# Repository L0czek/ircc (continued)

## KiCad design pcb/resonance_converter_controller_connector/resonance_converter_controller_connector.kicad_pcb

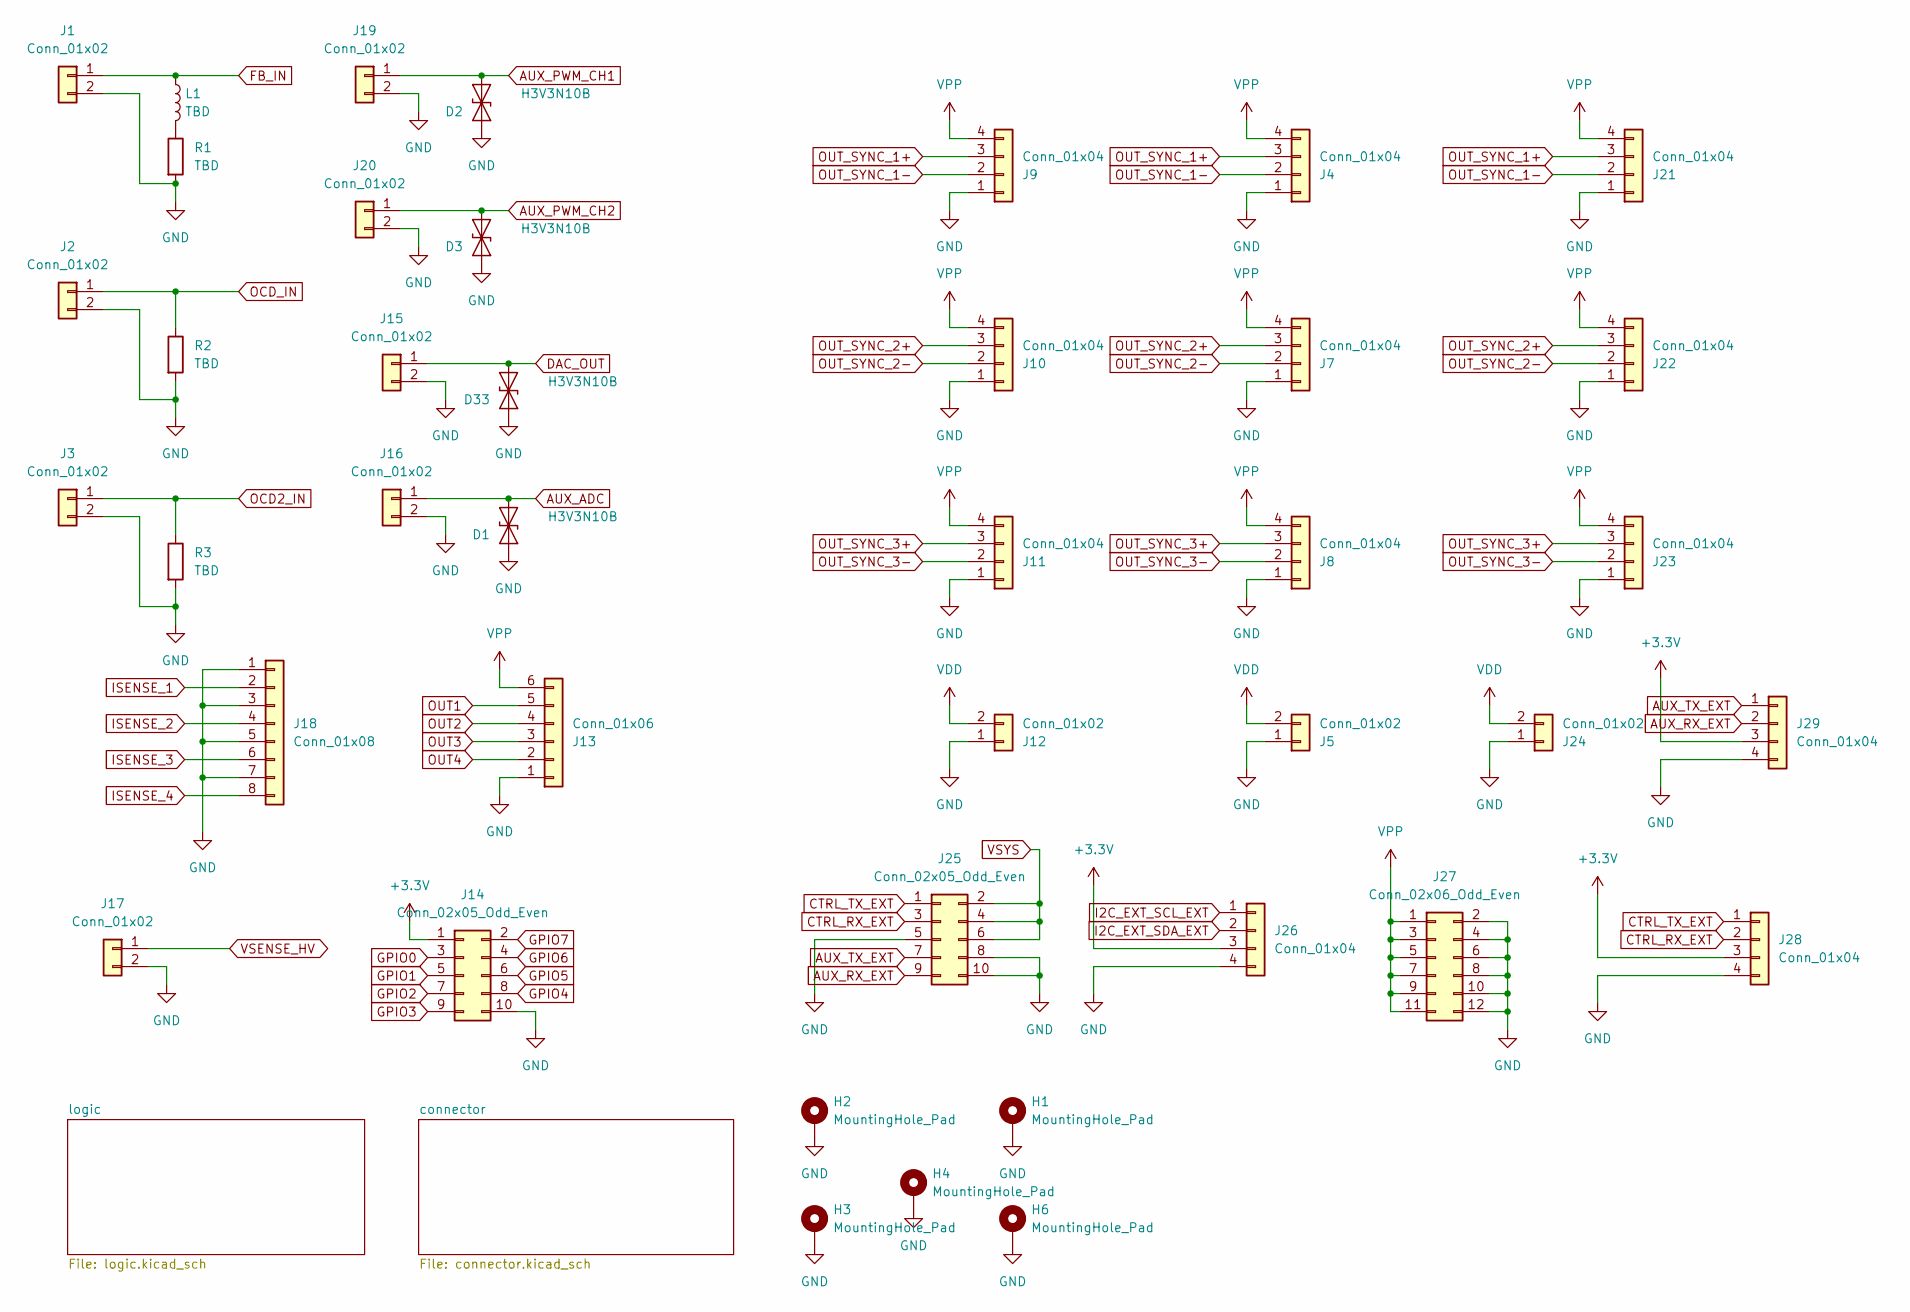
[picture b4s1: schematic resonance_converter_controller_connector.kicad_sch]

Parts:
D1, D2, D3, D33: H3V3N10B; D_0402_1005Metric; LCSC Part C20617909
H1, H2, H3, H4, H6: MountingHole_Pad; MountingHole_2.2mm_M2_Pad_Via
J1, J2, J3, J15, J16, J17, J19, J20: Conn_01x02; PhoenixContact_MCV_1,5_2-G-5.08_1x02_P5.08mm_Vertical
J4, J7, J8, J9, J10, J11, J21, J22, J23, J26, J28, J29: Conn_01x04; JST_PH_B4B-PH-K_1x04_P2.00mm_Vertical
J5, J12, J24: Conn_01x02; AMASS_XT30U-M_1x02_P5.0mm_Vertical
J13: Conn_01x06; JST_PH_B6B-PH-K_1x06_P2.00mm_Vertical
J14, J25: Conn_02x05_Odd_Even; PinHeader_2x05_P2.54mm_Vertical
J18: Conn_01x08; PhoenixContact_MCV_1,5_8-G-3.5_1x08_P3.50mm_Vertical
J27: Conn_02x06_Odd_Even; PinHeader_2x06_P2.54mm_Vertical
L1: TBD; L_Radial_D12.0mm_P10.00mm_Neosid_SD12_style1
R1, R2, R3: TBD; TO-220-2_Vertical

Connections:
+3.3V: J14.1, J26.3, J28.3, J29.3; also elsewhere on the board
AUX_ADC: D1.1 (A1), J16.1; also elsewhere on the board
AUX_PWM_CH1: D2.1 (A1), J19.1; also elsewhere on the board
AUX_PWM_CH2: D3.1 (A1), J20.1; also elsewhere on the board
AUX_RX_EXT: J25.9, J29.2; also elsewhere on the board
AUX_TX_EXT: J25.7, J29.1; also elsewhere on the board
CTRL_RX_EXT: J25.3, J28.2; also elsewhere on the board
CTRL_TX_EXT: J25.1, J28.1; also elsewhere on the board
DAC_OUT: D33.1 (A1), J15.1; also elsewhere on the board
FB_IN: J1.1, L1.1; also elsewhere on the board
GND: D1.2 (A2), D2.2 (A2), D3.2 (A2), D33.2 (A2), H1.1 (1_1), H2.1 (1_1), H3.1 (1_1), H4.1 (1_1), H6.1 (1_1), J1.2, J2.2, J3.2, J4.1, J5.1, J7.1, J8.1, J9.1, J10.1, J11.1, J12.1, J13.1, J14.10, J15.2, J16.2, J17.2, J18.1, J18.3, J18.5, J18.7, J19.2, J20.2, J21.1, J22.1, J23.1, J24.1, J25.5, J25.8, J25.10, J26.4, J27.2, J27.4, J27.6, J27.8, J27.10, J27.12, J28.4, J29.4, R1.2, R2.2, R3.2; also elsewhere on the board
GPIO0: J14.3; also elsewhere on the board
GPIO1: J14.5; also elsewhere on the board
GPIO2: J14.7; also elsewhere on the board
GPIO3: J14.9; also elsewhere on the board
GPIO4: J14.8; also elsewhere on the board
GPIO5: J14.6; also elsewhere on the board
GPIO6: J14.4; also elsewhere on the board
GPIO7: J14.2; also elsewhere on the board
I2C_EXT_SCL_EXT: J26.1; also elsewhere on the board
I2C_EXT_SDA_EXT: J26.2; also elsewhere on the board
ISENSE_1: J18.2; also elsewhere on the board
ISENSE_2: J18.4; also elsewhere on the board
ISENSE_3: J18.6; also elsewhere on the board
ISENSE_4: J18.8; also elsewhere on the board
unnamed: L1.2, R1.1
OCD2_IN: J3.1, R3.1; also elsewhere on the board
OCD_IN: J2.1, R2.1; also elsewhere on the board
OUT1: J13.5; also elsewhere on the board
OUT2: J13.4; also elsewhere on the board
OUT3: J13.3; also elsewhere on the board
OUT4: J13.2; also elsewhere on the board
OUT_SYNC_1+: J4.3, J9.3, J21.3; also elsewhere on the board
OUT_SYNC_1-: J4.2, J9.2, J21.2; also elsewhere on the board
OUT_SYNC_2+: J7.3, J10.3, J22.3; also elsewhere on the board
OUT_SYNC_2-: J7.2, J10.2, J22.2; also elsewhere on the board
OUT_SYNC_3+: J8.3, J11.3, J23.3; also elsewhere on the board
OUT_SYNC_3-: J8.2, J11.2, J23.2; also elsewhere on the board
VDD: J5.2, J12.2, J24.2; also elsewhere on the board
VPP: J4.4, J7.4, J8.4, J9.4, J10.4, J11.4, J13.6, J21.4, J22.4, J23.4, J27.1, J27.3, J27.5, J27.7, J27.9, J27.11; also elsewhere on the board
VSENSE_HV: J17.1; also elsewhere on the board
VSYS: J25.2, J25.4, J25.6; also elsewhere on the board

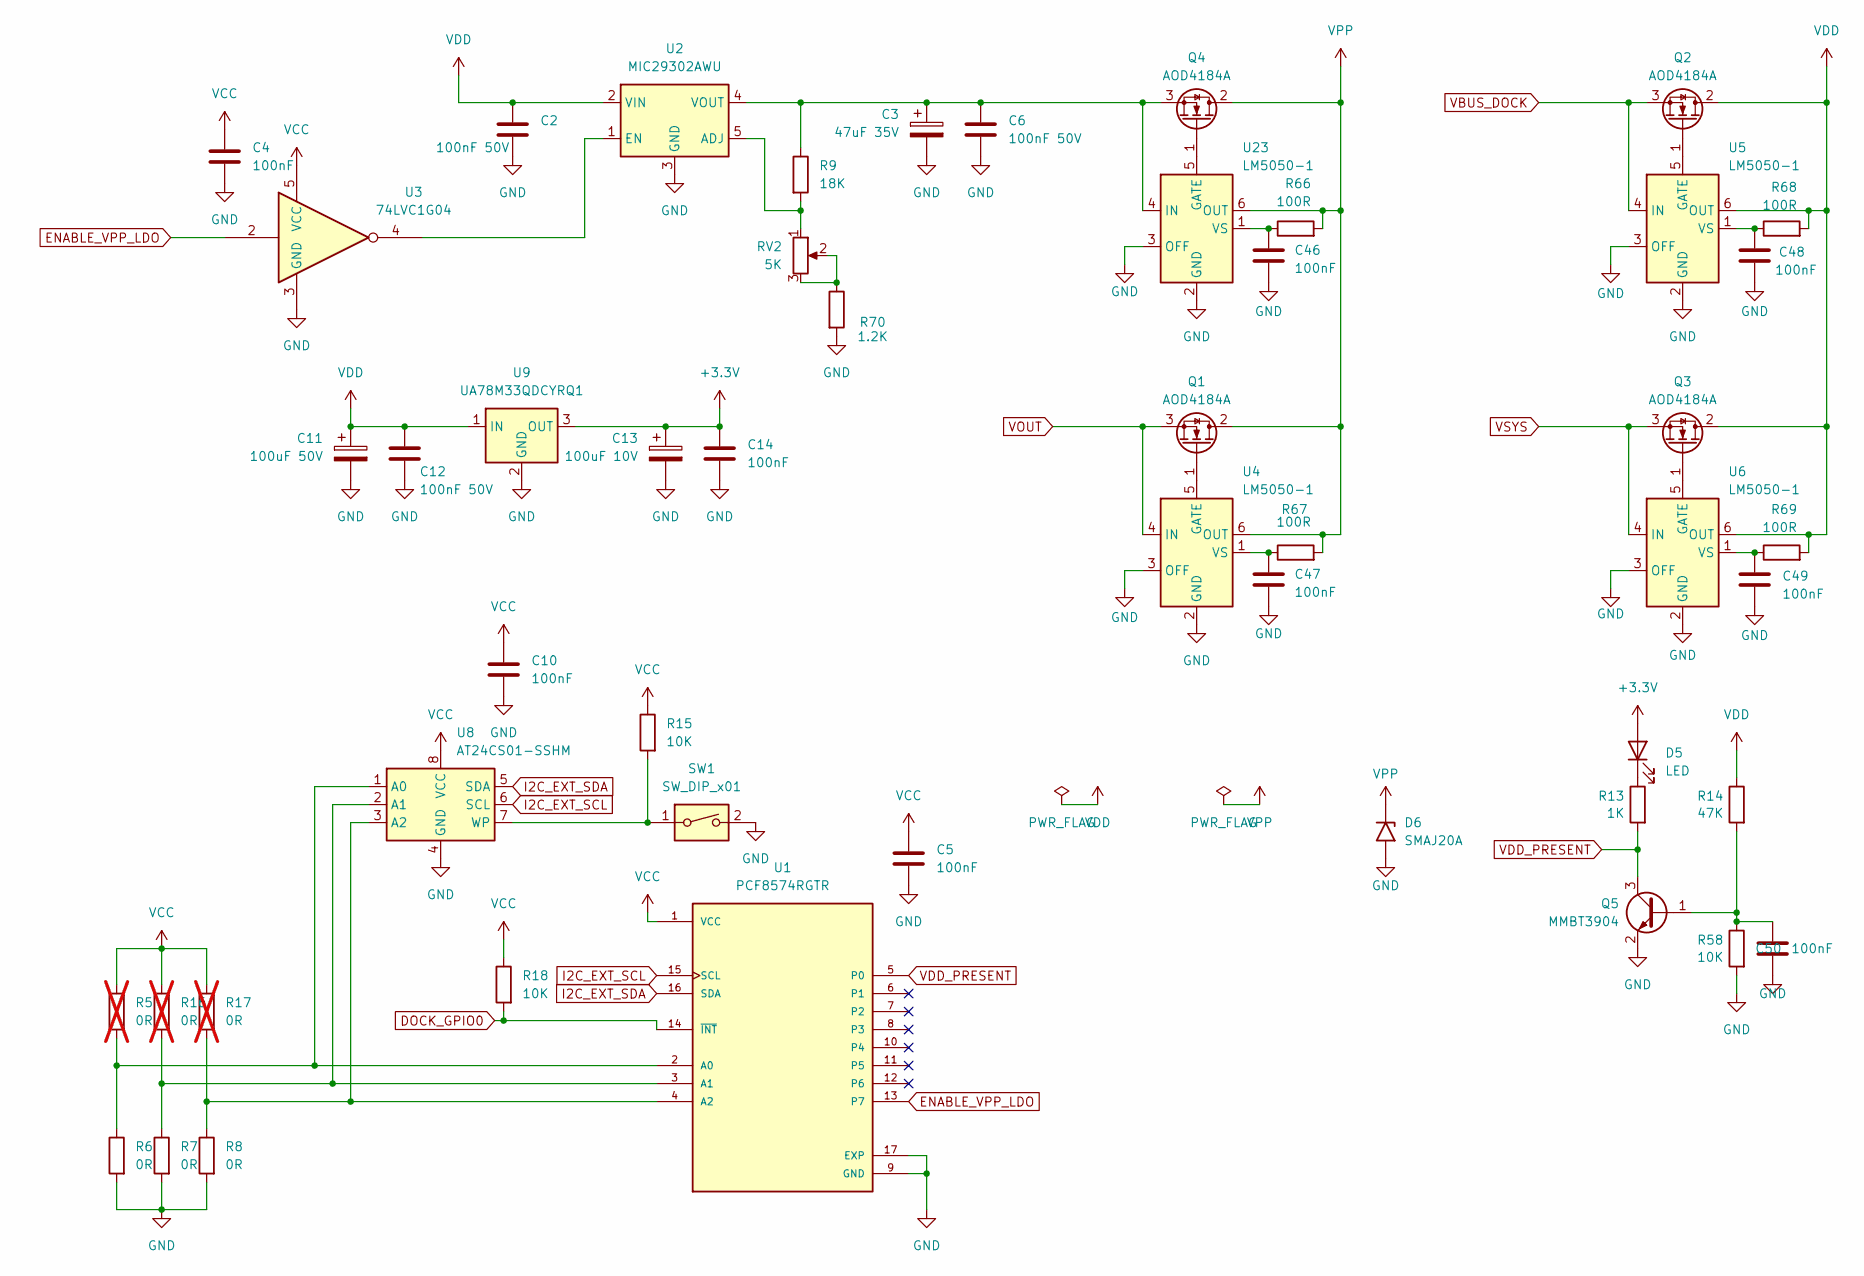
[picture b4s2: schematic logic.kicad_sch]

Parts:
C2, C6, C12: 100nF 50V; C_0603_1608Metric; LCSC Part C14663
C3: 47uF 35V; CP_Elec_10x10
C4, C5, C10, C14, C50: 100nF; C_0402_1005Metric; LCSC Part C307331
C11: 100uF 50V; CP_Elec_10x10
C13: 100uF 10V; CP_Elec_10x10
C46, C47, C48, C49: 100nF; C_0603_1608Metric; LCSC Part C14663
D5: LED; LED_1206_3216Metric
D6: SMAJ20A; D_SMA; MPN SMAJ20A; LCSC Part C41376408
Q1, Q2, Q3, Q4: AOD4184A; TO-252-2; MPN AOD4184A; LCSC Part C22367195
Q5: MMBT3904; SOT-23; MPN MMBT3904; LCSC Part C20526
R5, R16, R17: 0R; R_0402_1005Metric; LCSC Part C17168; not fitted
R6, R7, R8: 0R; R_0402_1005Metric; LCSC Part C17168
R9: 18K; R_0402_1005Metric; LCSC Part C25762
R13: 1K; R_0402_1005Metric; LCSC Part C11702
R14: 47K; R_0402_1005Metric; LCSC Part C25792
R15, R18, R58: 10K; R_0402_1005Metric; LCSC Part C25744
R66, R67, R68, R69: 100R; R_0402_1005Metric; LCSC Part C25076
R70: 1.2K; R_0402_1005Metric; LCSC Part C25862
RV2: 5K; Potentiometer_Bourns_3269W_Vertical
SW1: SW_DIP_x01; SW_DIP_SPSTx01_Slide_9.78x4.72mm_W8.61mm_P2.54mm
U1: PCF8574RGTR; QFN50P300X300X100-17N; PARTREV J; DigiKey_Part_Number 296-21238-1-ND
U2: MIC29302AWU; TO-263-5_TabPin3
U3: 74LVC1G04; SOT-23-5
U4, U5, U6, U23: LM5050-1; TSOT-23-6; MPN LM5050MK-1/NOPB; LCSC Part C129323
U8: AT24CS01-SSHM; SOIC-8_3.9x4.9mm_P1.27mm
U9: UA78M33QDCYRQ1; SOT-223-3_TabPin2

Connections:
+3.3V: C13.1, C14.1, D5.2 (A), U9.3 (OUT); also elsewhere on the board
DOCK_GPIO0: R18.2, U1.14 (~INT)
ENABLE_VPP_LDO: U1.13 (P7), U3.2
GND: C2.2, C3.2, C4.2, C5.2, C6.2, C10.2, C11.2, C12.2, C13.2, C14.2, C46.2, C47.2, C48.2, C49.2, C50.2, D6.2 (A2), Q5.2 (E), R6.2, R7.2, R8.2, R58.2, R70.2, SW1.2, U1.9 (GND), U1.17 (EXP), U2.3 (GND), U3.3 (GND), U4.2 (GND), U4.3 (OFF), U5.2 (GND), U5.3 (OFF), U6.2 (GND), U6.3 (OFF), U8.4 (GND), U9.2 (GND), U23.2 (GND), U23.3 (OFF); also elsewhere on the board
I2C_EXT_SCL: U1.15 (SCL), U8.6 (SCL); also elsewhere on the board
I2C_EXT_SDA: U1.16 (SDA), U8.5 (SDA); also elsewhere on the board
unnamed: D5.1 (K), R13.1
unnamed: Q1.1 (G), U4.5 (GATE)
unnamed: Q2.1 (G), U5.5 (GATE)
unnamed: Q3.1 (G), U6.5 (GATE)
unnamed: Q4.1 (G), U23.5 (GATE)
unnamed: C3.1, C6.1, Q4.3 (S), R9.1, U2.4 (VOUT), U23.4 (IN)
unnamed: C50.1, Q5.1 (B), R14.2, R58.1
unnamed: R70.1, RV2.2, RV2.3
unnamed: R5.2, R6.1, U1.2 (A0), U8.1 (A0)
unnamed: R7.1, R16.2, U1.3 (A1), U8.2 (A1)
unnamed: R8.1, R17.2, U1.4 (A2), U8.3 (A2)
unnamed: R9.2, RV2.1, U2.5 (ADJ)
unnamed: U2.1 (EN), U3.4
unnamed: C47.1, R67.1, U4.1 (VS)
unnamed: C48.1, R68.1, U5.1 (VS)
unnamed: C49.1, R69.1, U6.1 (VS)
unnamed: R15.2, SW1.1, U8.7 (WP)
unnamed: C46.1, R66.1, U23.1 (VS)
VBUS_DOCK: Q2.3 (S), U5.4 (IN); also elsewhere on the board
VCC: C4.1, C5.1, C10.1, R5.1, R15.1, R16.1, R17.1, R18.1, U1.1 (VCC), U3.5 (VCC), U8.8 (VCC); also elsewhere on the board
VDD: C2.1, C11.1, C12.1, Q2.2 (D), Q3.2 (D), R14.1, R68.2, R69.2, U2.2 (VIN), U5.6 (OUT), U6.6 (OUT), U9.1 (IN); also elsewhere on the board
VDD_PRESENT: Q5.3 (C), R13.2, U1.5 (P0)
VOUT: Q1.3 (S), U4.4 (IN); also elsewhere on the board
VPP: D6.1 (A1), Q1.2 (D), Q4.2 (D), R66.2, R67.2, U4.6 (OUT), U23.6 (OUT); also elsewhere on the board
VSYS: Q3.3 (S), U6.4 (IN); also elsewhere on the board

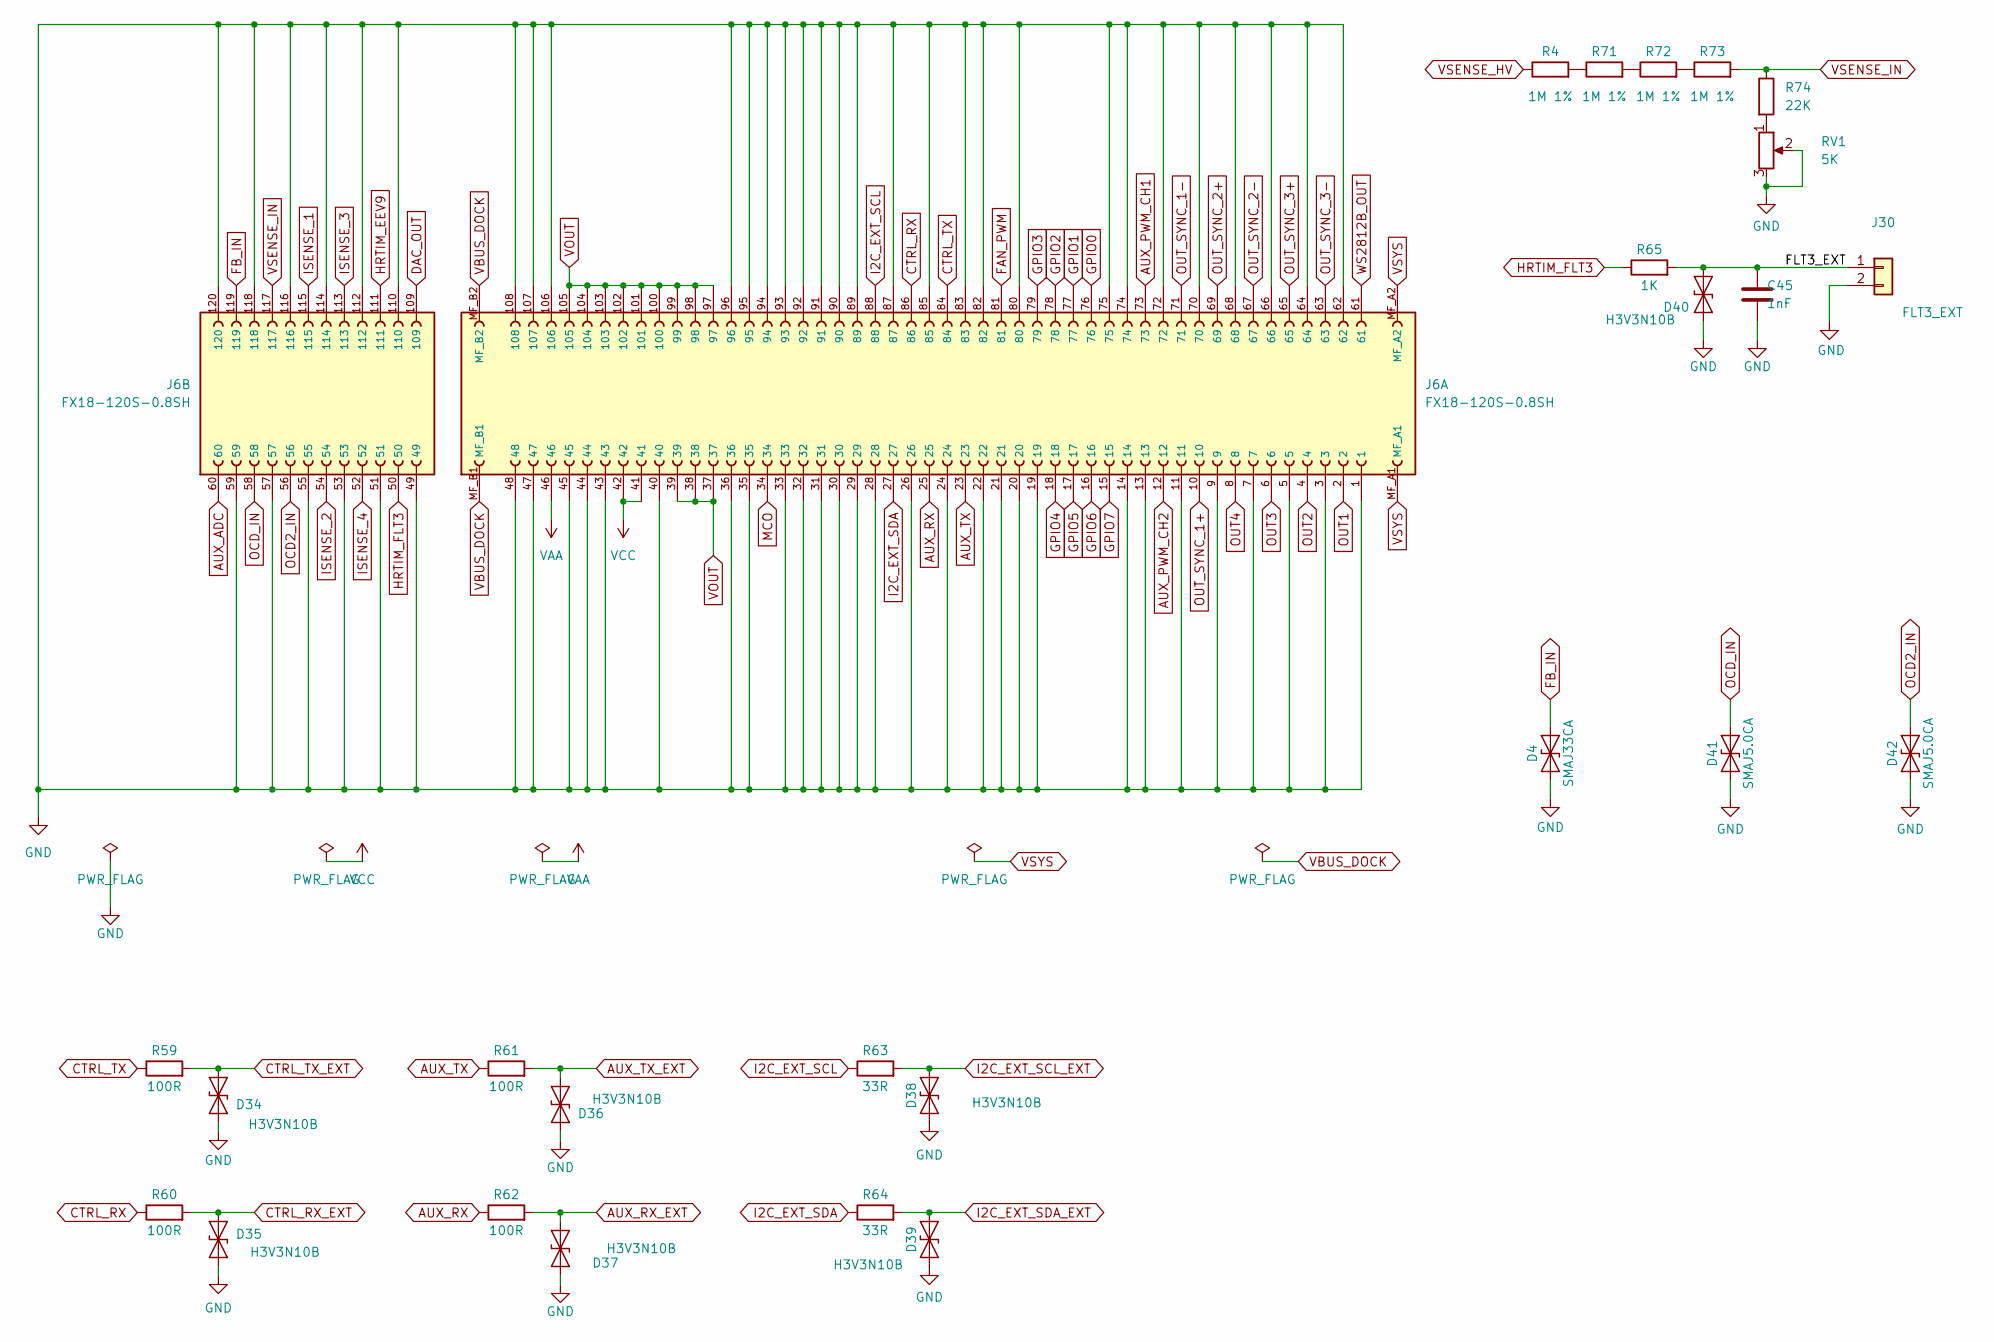
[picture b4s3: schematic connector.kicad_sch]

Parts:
C45: 1nF; C_0402_1005Metric; LCSC Part C1523
D4: SMAJ33CA; D_SMA; MPN SMAJ33CA; LCSC Part C19077549
D34, D35, D36, D37, D38, D39, D40: H3V3N10B; D_0402_1005Metric; LCSC Part C20617909
D41, D42: SMAJ5.0CA; D_SMA; MPN SMAJ5.0CA; LCSC Part C19077524
J6: FX18-120S-0.8SH; HIROSE_FX18-120S-0.8SH; PARTREV 1
J30: FLT3_EXT; PinHeader_1x02_P2.54mm_Vertical
R4, R71, R72, R73: 1M 1%; R_1206_3216Metric; LCSC Part C17927
R59, R60, R61, R62: 100R; R_0402_1005Metric; LCSC Part C25076
R63, R64: 33R; R_0402_1005Metric; LCSC Part C25105
R65: 1K; R_0402_1005Metric; LCSC Part C11702
R74: 22K; R_0402_1005Metric; LCSC Part C25768
RV1: 5K; Potentiometer_Bourns_3269W_Vertical

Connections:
/connector/FLT3_EXT: C45.1, D40.2 (A2), J30.1, R65.2
AUX_ADC: J6.60; also elsewhere on the board
AUX_PWM_CH1: J6.73; also elsewhere on the board
AUX_PWM_CH2: J6.12; also elsewhere on the board
AUX_RX: J6.25, R62.1
AUX_RX_EXT: D37.2 (A2), R62.2; also elsewhere on the board
AUX_TX: J6.23, R61.1
AUX_TX_EXT: D36.2 (A2), R61.2; also elsewhere on the board
CTRL_RX: J6.86, R60.1
CTRL_RX_EXT: D35.2 (A2), R60.2; also elsewhere on the board
CTRL_TX: J6.84, R59.1
CTRL_TX_EXT: D34.2 (A2), R59.2; also elsewhere on the board
DAC_OUT: J6.109; also elsewhere on the board
FAN_PWM: J6.81
FB_IN: D4.2 (A2), J6.119; also elsewhere on the board
GND: C45.2, D4.1 (A1), D34.1 (A1), D35.1 (A1), D36.1 (A1), D37.1 (A1), D38.1 (A1), D39.1 (A1), D40.1 (A1), D41.1 (A1), D42.1 (A1), J6.1, J6.3, J6.5, J6.7, J6.9, J6.11, J6.13, J6.14, J6.19, J6.20, J6.21, J6.22, J6.24, J6.26, J6.28, J6.29, J6.30, J6.31, J6.32, J6.33, J6.35, J6.36, J6.40, J6.43, J6.44, J6.45, J6.47, J6.48, J6.49, J6.51, J6.53, J6.55, J6.57, J6.59, J6.62, J6.64, J6.66, J6.68, J6.70, J6.72, J6.74, J6.75, J6.80, J6.82, J6.83, J6.85, J6.87, J6.89, J6.90, J6.91, J6.92, J6.93, J6.94, J6.95, J6.96, J6.106, J6.107, J6.108, J6.110, J6.112, J6.114, J6.116, J6.118, J6.120, J30.2, RV1.2, RV1.3; also elsewhere on the board
GPIO0: J6.76; also elsewhere on the board
GPIO1: J6.77; also elsewhere on the board
GPIO2: J6.78; also elsewhere on the board
GPIO3: J6.79; also elsewhere on the board
GPIO4: J6.18; also elsewhere on the board
GPIO5: J6.17; also elsewhere on the board
GPIO6: J6.16; also elsewhere on the board
GPIO7: J6.15; also elsewhere on the board
HRTIM_EEV9: J6.111
HRTIM_FLT3: J6.50, R65.1
I2C_EXT_SCL: J6.88, R63.1; also elsewhere on the board
I2C_EXT_SCL_EXT: D38.2 (A2), R63.2; also elsewhere on the board
I2C_EXT_SDA: J6.27, R64.1; also elsewhere on the board
I2C_EXT_SDA_EXT: D39.2 (A2), R64.2; also elsewhere on the board
ISENSE_1: J6.115; also elsewhere on the board
ISENSE_2: J6.54; also elsewhere on the board
ISENSE_3: J6.113; also elsewhere on the board
ISENSE_4: J6.52; also elsewhere on the board
MCO: J6.34
unnamed: R4.2, R71.1
unnamed: R71.2, R72.1
unnamed: R72.2, R73.1
unnamed: R74.2, RV1.1
OCD2_IN: D42.2 (A2), J6.56; also elsewhere on the board
OCD_IN: D41.2 (A2), J6.58; also elsewhere on the board
OUT1: J6.2; also elsewhere on the board
OUT2: J6.4; also elsewhere on the board
OUT3: J6.6; also elsewhere on the board
OUT4: J6.8; also elsewhere on the board
OUT_SYNC_1+: J6.10; also elsewhere on the board
OUT_SYNC_1-: J6.71; also elsewhere on the board
OUT_SYNC_2+: J6.69; also elsewhere on the board
OUT_SYNC_2-: J6.67; also elsewhere on the board
OUT_SYNC_3+: J6.65; also elsewhere on the board
OUT_SYNC_3-: J6.63; also elsewhere on the board
VAA: J6.46
VBUS_DOCK: J6.MF_B1, J6.MF_B2; also elsewhere on the board
VCC: J6.41, J6.42; also elsewhere on the board
VOUT: J6.37, J6.38, J6.39, J6.97, J6.98, J6.99, J6.100, J6.101, J6.102, J6.103, J6.104, J6.105; also elsewhere on the board
VSENSE_HV: R4.1; also elsewhere on the board
VSENSE_IN: J6.117, R73.2, R74.1
VSYS: J6.MF_A1, J6.MF_A2; also elsewhere on the board
WS2812B_OUT: J6.61

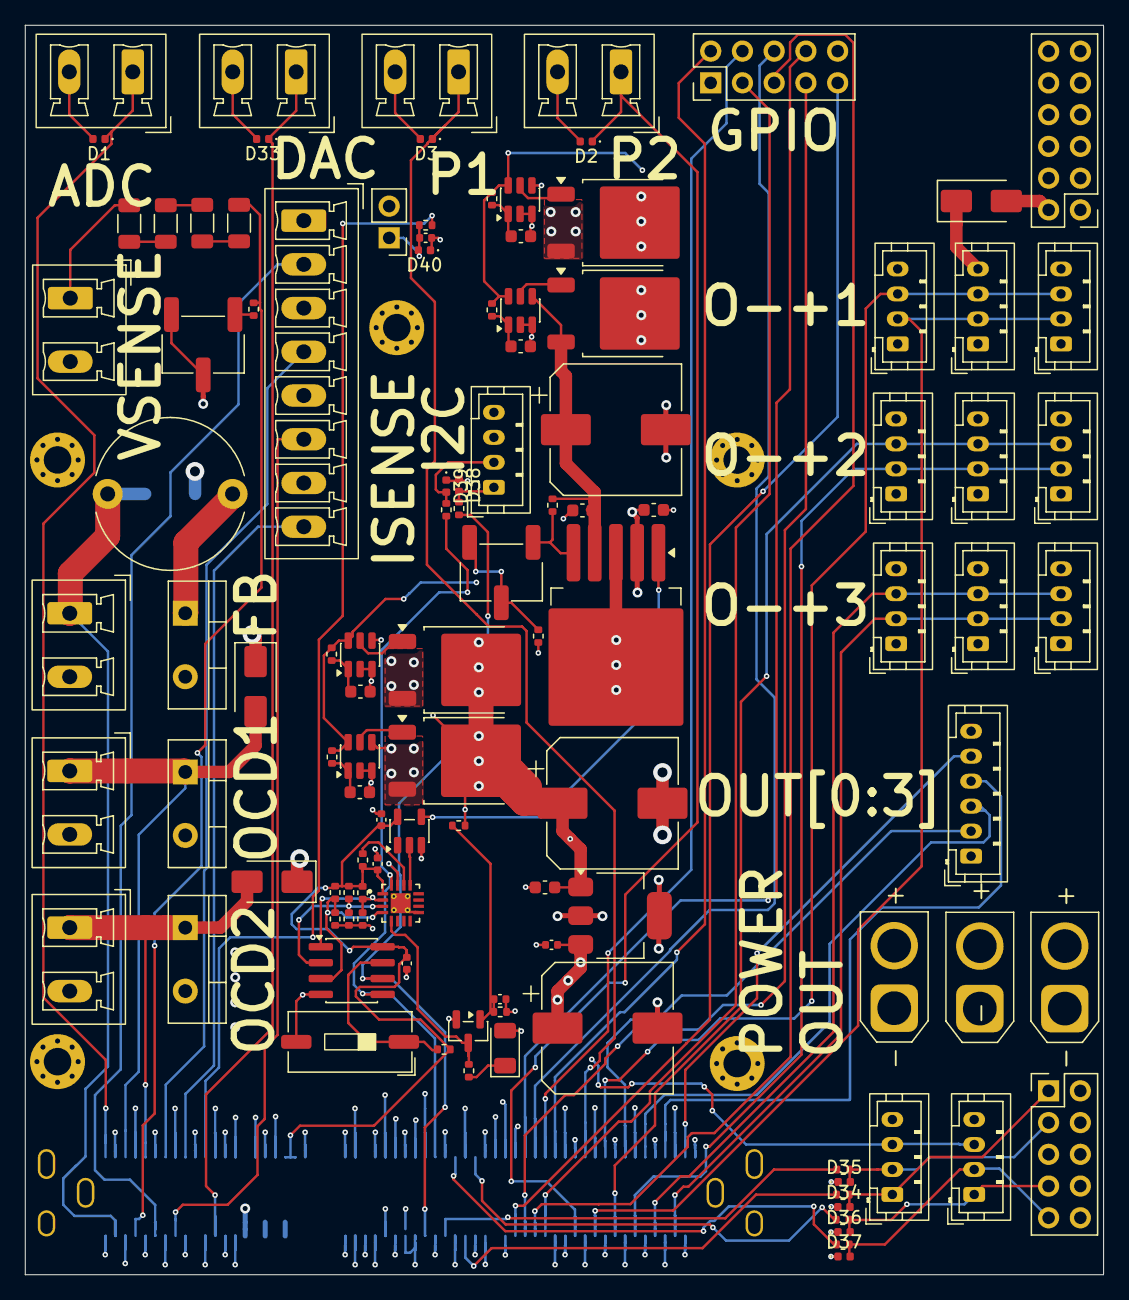
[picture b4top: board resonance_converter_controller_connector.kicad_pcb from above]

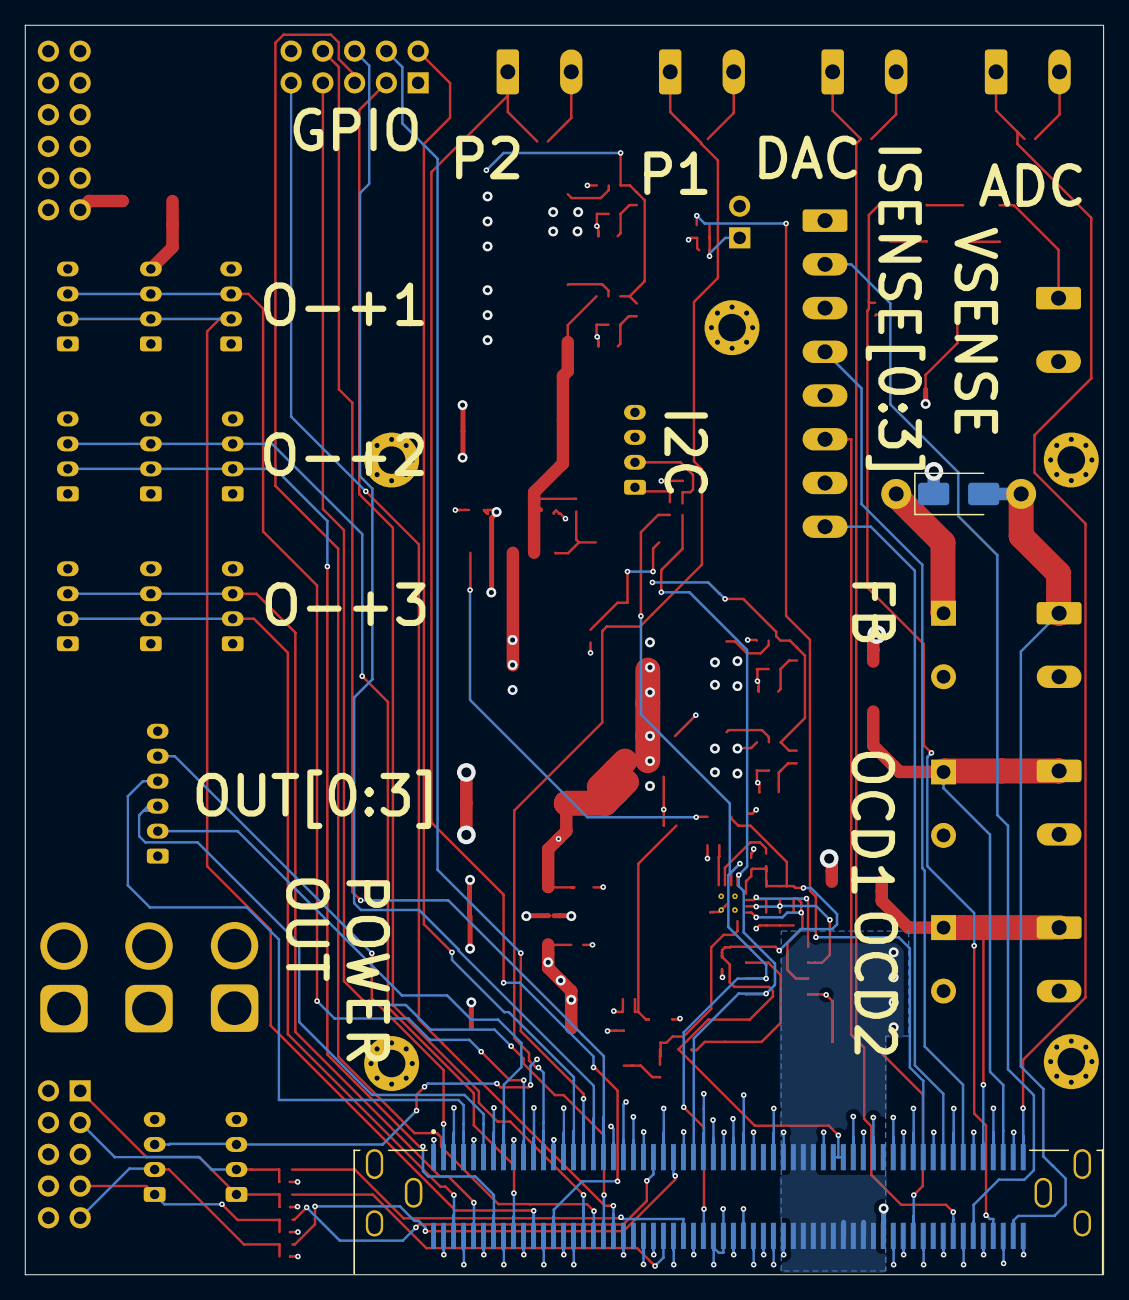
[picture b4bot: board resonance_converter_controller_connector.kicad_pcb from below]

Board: 4 copper layers, 86.3 x 100.0 mm, 117 parts (2 on the bottom side), 79 nets.

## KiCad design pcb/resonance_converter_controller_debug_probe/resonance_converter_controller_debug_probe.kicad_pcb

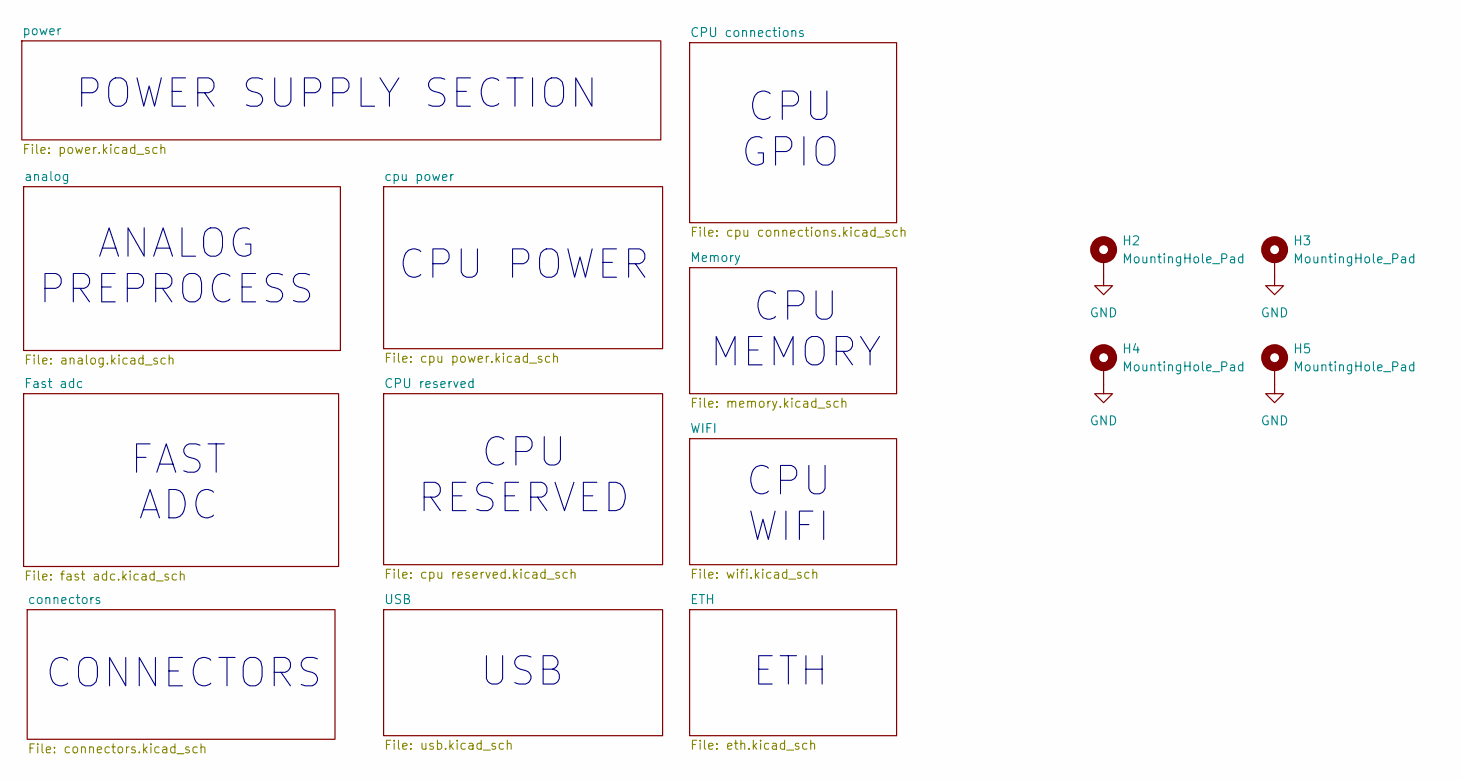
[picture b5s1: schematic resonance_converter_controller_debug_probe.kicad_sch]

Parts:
H2, H3, H4, H5: MountingHole_Pad; MountingHole_2.5mm_Pad_Via

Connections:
GND: H2.1 (1_1), H3.1 (1_1), H4.1 (1_1), H5.1 (1_1); also elsewhere on the board

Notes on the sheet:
CONNECTORS
CPU RESERVED
CPU GPIO
FAST ADC
ANALOG PREPROCESS
CPU MEMORY
USB
ETH
CPU POWER
CPU WIFI
POWER SUPPLY SECTION
